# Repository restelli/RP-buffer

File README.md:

# Multiplying Buffer for Red Pitaya designs

See the design with kicanvas by [following this link](https://kicanvas.org/?repo=https%3A%2F%2Fgithub.com%2Frestelli%2FRP-buffer%2Ftree%2Fmain%2Fkicad)

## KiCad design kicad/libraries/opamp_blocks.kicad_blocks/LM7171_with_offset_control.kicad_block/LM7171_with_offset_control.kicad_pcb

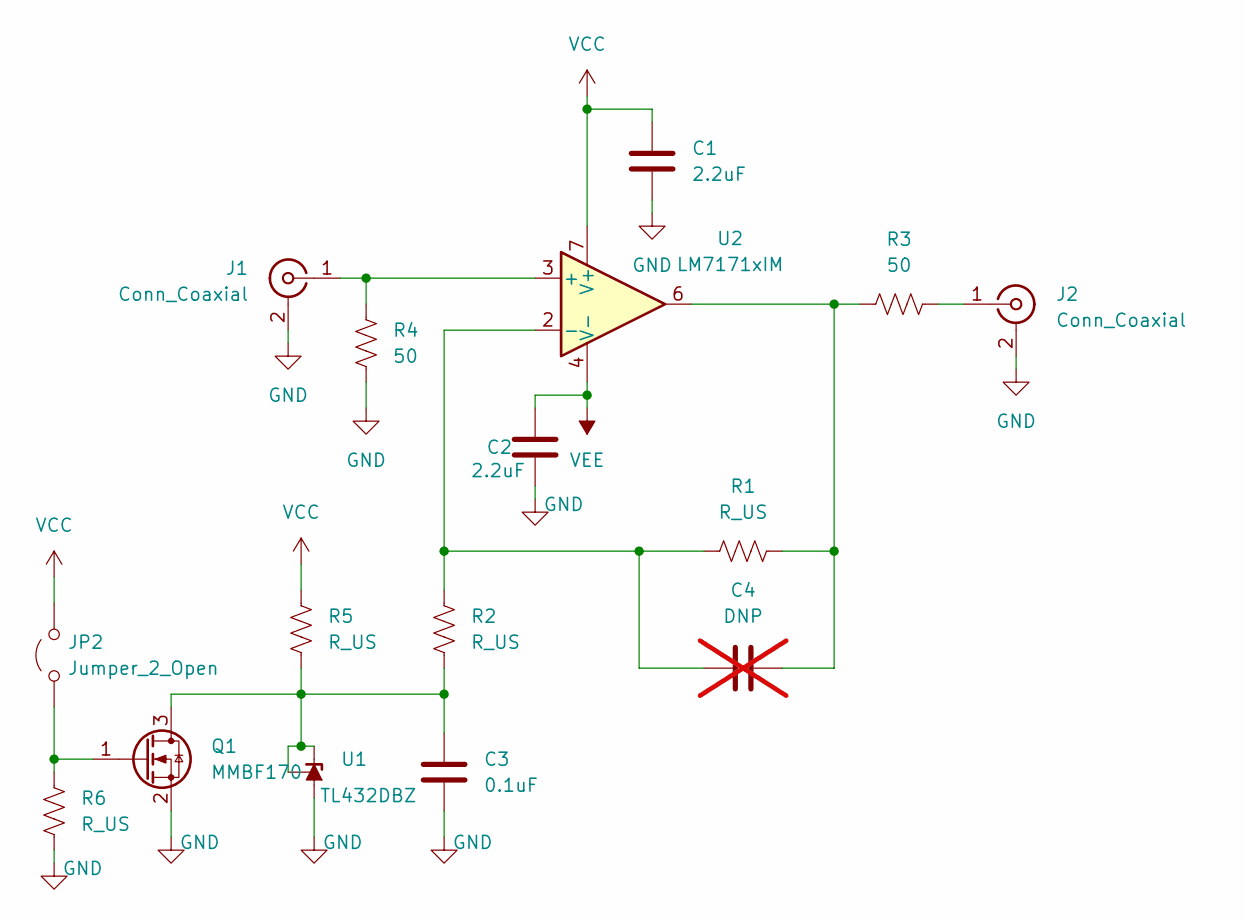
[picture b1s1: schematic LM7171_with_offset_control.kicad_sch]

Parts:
C1, C2: 2.2uF; C_0805_2012Metric_Pad1.18x1.45mm_HandSolder
C3: 0.1uF; C_0805_2012Metric
C4: DNP; C_0603_1608Metric; not fitted
J1: Conn_Coaxial; SMA_Amphenol_132291-12_Vertical
J2: Conn_Coaxial; SMA_Amphenol_132134-16_Vertical
JP2: Jumper_2_Open; TerminalBlock_Xinya_XY308-2.54-2P_1x02_P2.54mm_Horizontal
Q1: MMBF170; SOT-23
R1, R2, R5, R6: R_US; R_0603_1608Metric
R3, R4: 50; R_1206_3216Metric_Pad1.30x1.75mm_HandSolder
U1: TL432DBZ; SOT-23
U2: LM7171xIM; SOIC-8_3.9x4.9mm_P1.27mm

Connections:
GND: C1.2, C2.2, C3.2, J1.2 (Ext), J2.2 (Ext), Q1.2 (S), R4.1, R6.1, U1.3 (A)
unnamed: C4.2, R1.2, R3.1, U2.6
unnamed: J1.1 (In), R4.2, U2.3 (+)
unnamed: J2.1 (In), R3.2
unnamed: JP2.1 (A), Q1.1 (G), R6.2
unnamed: C3.1, Q1.3 (D), R2.1, R5.1, U1.1 (REF), U1.2 (K)
unnamed: C4.1, R1.1, R2.2, U2.2 (-)
VCC: C1.1, JP2.2 (B), R5.2, U2.7 (V+)
VEE: C2.1, U2.4 (V-)

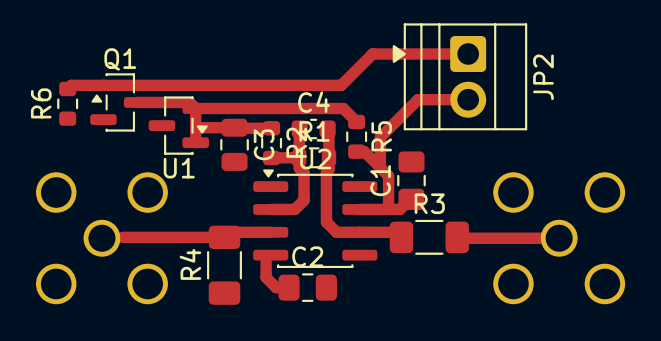
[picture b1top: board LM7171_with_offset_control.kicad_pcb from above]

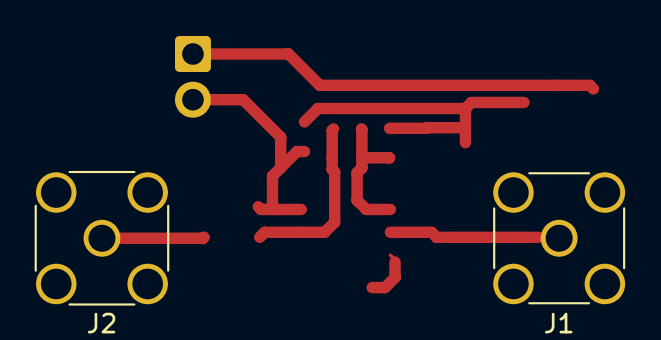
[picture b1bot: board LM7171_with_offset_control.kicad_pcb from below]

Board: 2 copper layers, 16 parts (2 on the bottom side), 9 nets.
